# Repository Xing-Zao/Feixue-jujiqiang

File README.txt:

00_Priority README ------------- 技术文档，首先阅读
01_Firmware --------------------- 软件相关文件夹
02_Electronics -------------------- 电路相关文件夹
03_Machines --------------------- 机械相关文件夹
04_others ------------------------ 其他文件

README,txt --------------------- 每个分类文件夹都有，含有所处文件夹的阅读索引及必要说明，请最先阅读

相关源文件，软件可能不支持中文路径名，所以请先将项目名称改为中文

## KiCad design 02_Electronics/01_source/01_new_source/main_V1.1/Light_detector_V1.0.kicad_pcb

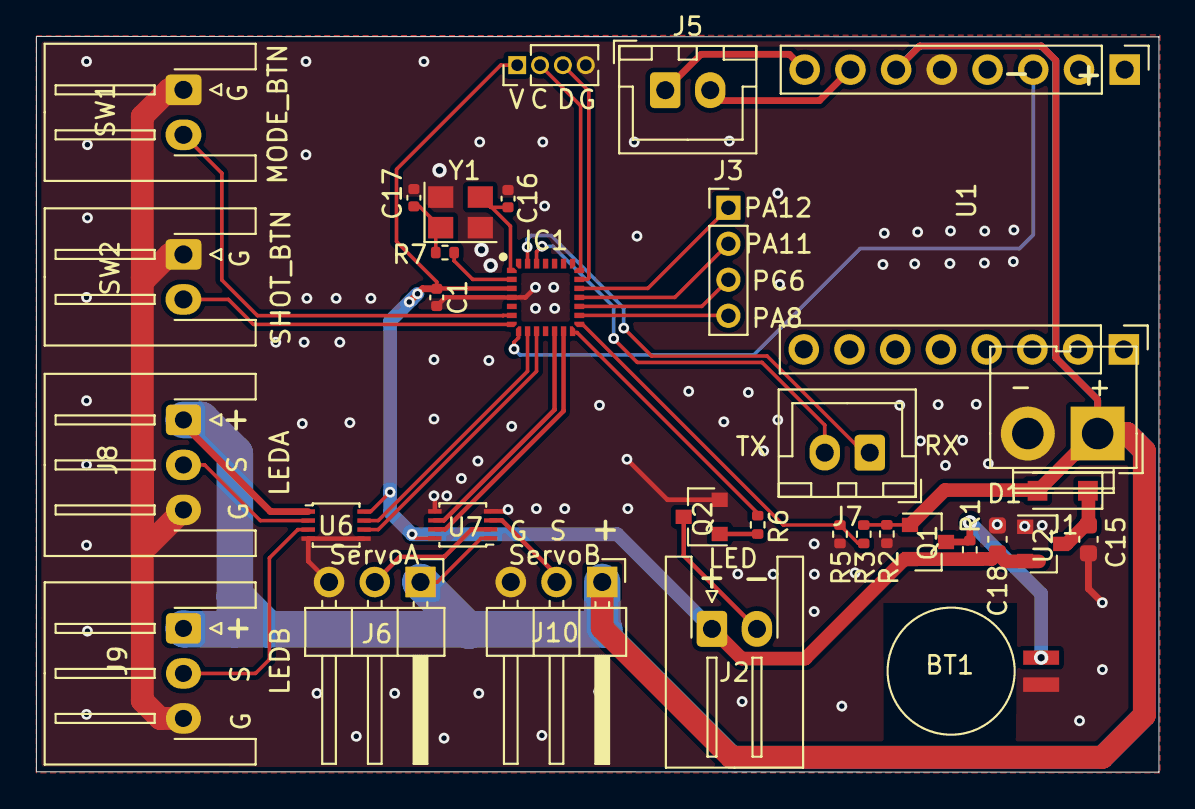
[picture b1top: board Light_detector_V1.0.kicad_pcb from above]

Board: 2 copper layers, 62.4 x 40.9 mm, 33 parts (0 on the bottom side), 33 nets.

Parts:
BT1: MS621FE; BatteryHolder_Seiko_MS621F
C1: 0.1uF; C_0402_1005Metric
C15, C18: 1uF; C_0603_1608Metric
C16, C17: 20pF; C_0402_1005Metric
D1: SS314F; D_SOD-123F
IC1: STM32G031G6U6; UFQFPN28
J1: POWER; JWT_A3963_1x02_P3.96mm_Vertical
J2: R_LED; JST_XH_S2B-XH-A-1_1x02_P2.50mm_Horizontal
J3: EXT; PinHeader_1x04_P2.00mm_Vertical
J4: SWD; PinHeader_1x04_P1.27mm_Vertical
J5: SPK; JST_XH_B2B-XH-A_1x02_P2.50mm_Vertical
J6: SERVOA; PinHeader_1x03_P2.54mm_Horizontal
J7: UART; JST_XH_B2B-XH-A_1x02_P2.50mm_Vertical
J8, J9: LEDA; JST_XH_S3B-XH-A-1_1x03_P2.50mm_Horizontal
J10: SERVOB; PinHeader_1x03_P2.54mm_Horizontal
Q1: AO3400; SOT-23
Q2: SS8050; SOT-23
R1: 680R; R_0402_1005Metric
R2: 100K; R_0402_1005Metric
R3, R5: 1M; R_0402_1005Metric
R6: 1K; R_0402_1005Metric
R7: 390R; R_0402_1005Metric
SW1: MODE_BTN; JST_XH_S2B-XH-A-1_1x02_P2.50mm_Horizontal
SW2: SHOT_BTN; JST_XH_S2B-XH-A-1_1x02_P2.50mm_Horizontal
U1: JQ8900-16P
U2: XC6206; SOT-23
U6, U7: SN74LVC2T45DCUR; VSSOP-8_2.4x2.1mm_P0.5mm
Y1: 8MHz; Crystal_SMD_3225-4Pin_3.2x2.5mm

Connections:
+3V3: C1.1, C18.1, IC1.3, J2.1, J4.1, Q1.2, R1.2, U2.2, U6.8, U7.8
+5V: D1.2, J1.1, J6.1, J8.1, J9.1, J10.1, Q1.1, R2.2, R3.2, U1.6, U6.1, U7.1
/5V_check: IC1.15, R3.1, R5.2
/LEDC_DI_IN: IC1.9, U6.7
/LEDC_DI_OUT: J8.2, U6.2
/LEDD_DI_IN: IC1.10, U6.6
/LEDD_DI_OUT: J9.2, U6.3
/LED_R: IC1.14, R6.1
/MODE_KEY: IC1.6, SW1.2
/OSC_IN: C16.2, IC1.1, Y1.3
/OSC_OUT: IC1.2, R7.2
/RX: IC1.27, J7.1
/SERVOA_IN: IC1.13, U7.7
/SERVOA_OUT: J6.2, U7.2
/SERVOB_IN: IC1.12, U7.6
/SERVOB_OUT: J10.2, U7.3
/SHOT_KEY: IC1.7, SW2.2
/SPK_TX: IC1.8, U1.3
/SWCLK: IC1.21, J4.2
/SWDIO: IC1.20, J4.3
/TX: IC1.26, J7.2
Earth: BT1.2, C1.2, C15.2, C16.1, C17.1, C18.2, IC1.4, J1.2, J4.4, J6.3, J8.3, J9.3, J10.3, Q2.2, R2.1, R5.1, SW1.1, SW2.1, U1.5, U2.1, U6.4, U6.5, U7.4, U7.5, Y1.2, Y1.4
unnamed: BT1.1, Q1.3, R1.1
unnamed: C15.1, D1.1, U2.3
unnamed: C17.2, R7.1, Y1.1
unnamed: IC1.16, J3.4
unnamed: IC1.17, J3.3
unnamed: IC1.18, J3.2
unnamed: IC1.19, J3.1
unnamed: J2.2, Q2.3
unnamed: J5.1, U1.8
unnamed: J5.2, U1.7
unnamed: Q2.1, R6.2

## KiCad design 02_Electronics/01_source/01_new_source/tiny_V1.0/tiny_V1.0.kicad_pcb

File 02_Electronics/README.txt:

01_source ----------------------------------------- 存放软件源码和已迭代源码

02_tools ------------------------------------------- 程序编写相关软件及使用文档

03_documents ------------------------------------ PCB设计参考文档，含元器件手册

04_others ----------------------------------------- 其他文件

README.txt  -------------------------------------- 每个文件夹下都有该文件，为所处文件夹的阅读索引及必要说明

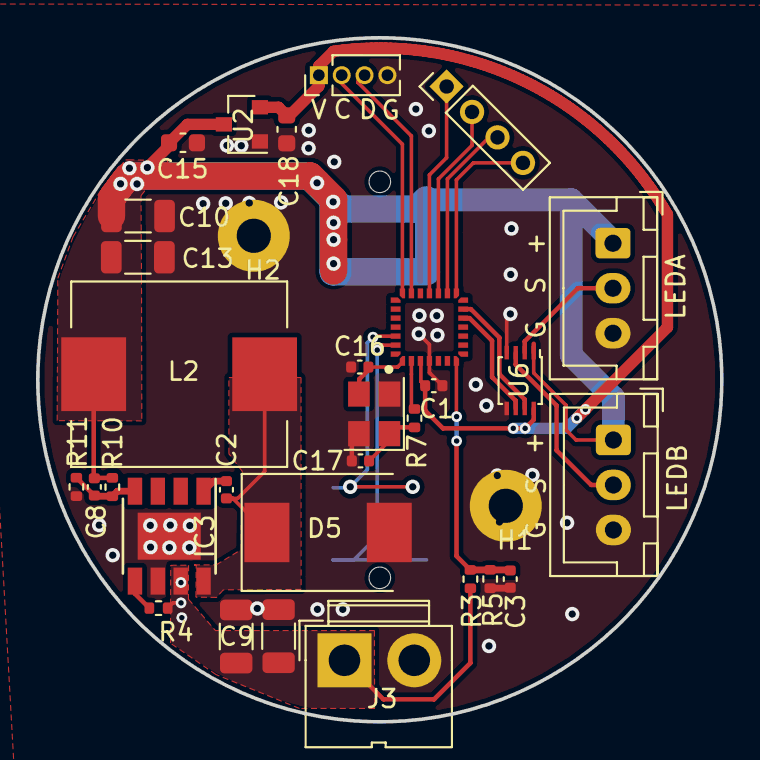
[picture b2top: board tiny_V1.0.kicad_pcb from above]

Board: 2 copper layers, 38.0 x 38.0 mm, 33 parts (1 on the bottom side), 24 nets.

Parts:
C1, C3: 0.1uF; C_0402_1005Metric
C2: 10nF; C_0402_1005Metric
C8: 82pF; C_0402_1005Metric
C9, C24: 4.7uF; C_1206_3216Metric
C10, C13: 22uF; C_1206_3216Metric
C15, C18: 1uF; C_0603_1608Metric
C16, C17: 20pF; C_0402_1005Metric
D5: B550C; D_SMC
H1, H2: MountingHole; MountingHole_1.5x4mm
IC1: STM32G031G6U6; UFQFPN28
IC3: RT8279GSP; Diodes_SO-8EP
J1: Conn_01x06; JL-6P-4.0PH-1.9H
J2: EXT; PinHeader_1x04_P2.00mm_Vertical
J3: Conn_01x02; JWT_A3963_1x02_P3.96mm_Vertical
J4: SWD; PinHeader_1x04_P1.27mm_Vertical
J8, J9: LEDA; JST_XH_B3B-XH-A_1x03_P2.50mm_Vertical
L2: 15uH; L_Neosid_SM-PIC1004H
R3: 2M; R_0402_1005Metric
R4, R10: 100K; R_0402_1005Metric
R5: 1M; R_0402_1005Metric
R7: 390R; R_0402_1005Metric
R11: 31.6k; R_0402_1005Metric
U2: XC6206; SOT-23
U6: SN74LVC2T45DCUR; VSSOP-8_2.4x2.1mm_P0.5mm
Y1: 8MHz; Crystal_SMD_3225-4Pin_3.2x2.5mm

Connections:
+3V3: C1.1, C18.1, IC1.3, J4.1, U2.2, U6.8
+5V: C8.2, C10.2, C13.2, C15.1, J1.1, J1.2, J8.1, J9.1, L2.2, R10.2, U2.3, U6.1
/BAT+: C9.1, C24.1, IC3.7, J3.1, R3.2, R4.1
/BAT_ADC: C3.1, IC1.7, R3.1, R5.2
/FB: C8.1, IC3.4, R10.1, R11.2
/LEDC_DI_IN: IC1.13, U6.7
/LEDC_DI_OUT: J8.2, U6.2
/LEDD_DI_IN: IC1.12, U6.6
/LEDD_DI_OUT: J9.2, U6.3
/OSC_IN: C16.2, IC1.1, Y1.3
/OSC_OUT: IC1.2, R7.2
/RX: IC1.27, J1.6
/SWCLK: IC1.21, J4.2
/SWDIO: IC1.20, J4.3
/TX: IC1.26, J1.5
Earth: C1.2, C3.2, C9.2, C10.1, C13.1, C15.2, C16.1, C17.1, C18.2, C24.2, D5.2, IC1.4, IC3.6, IC3.9, J1.3, J1.4, J3.2, J4.4, J8.3, J9.3, R5.1, R11.1, U2.1, U6.4, U6.5, Y1.2, Y1.4
unnamed: C2.1, D5.1, IC3.8, L2.1
unnamed: C2.2, IC3.1
unnamed: C17.2, R7.1, Y1.1
unnamed: IC1.15, J2.4
unnamed: IC1.16, J2.3
unnamed: IC1.17, J2.2
unnamed: IC1.18, J2.1
unnamed: IC3.5, R4.2

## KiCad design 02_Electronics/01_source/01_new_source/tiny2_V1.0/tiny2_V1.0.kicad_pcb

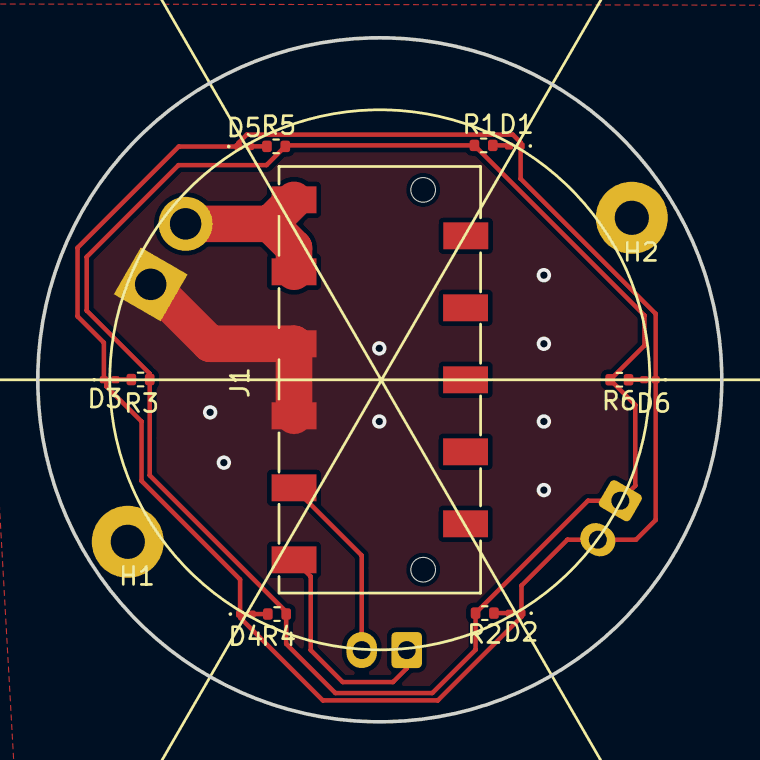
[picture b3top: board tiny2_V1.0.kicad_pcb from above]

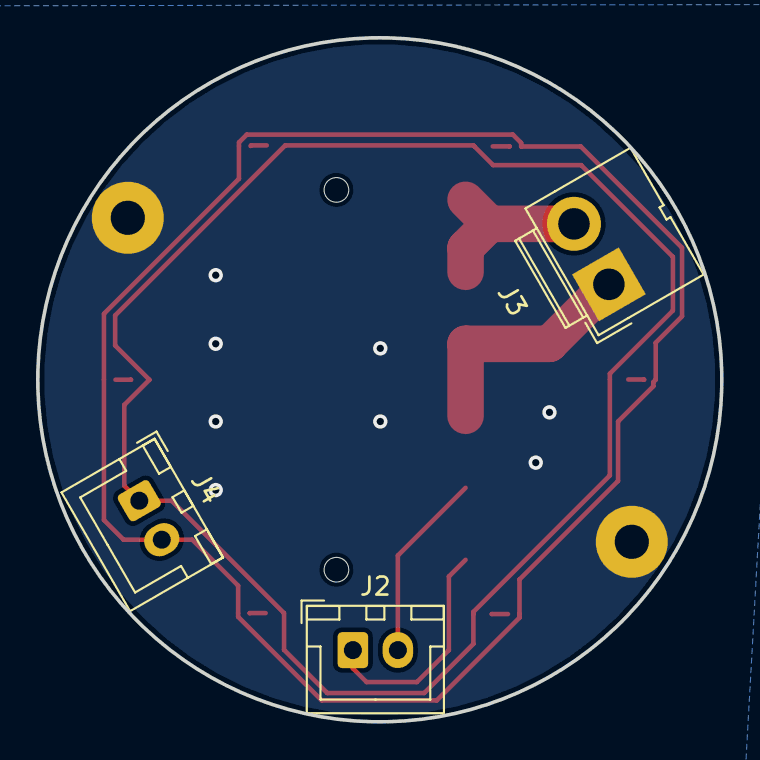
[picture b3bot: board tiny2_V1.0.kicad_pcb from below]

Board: 2 copper layers, 38.0 x 38.0 mm, 18 parts (3 on the bottom side), 12 nets.

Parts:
D1, D2, D3, D4, D5, D6: LED_Small; LED_0201_0603Metric
H1, H2: MountingHole; MountingHole_1.5x4mm
J1: Conn_01x06; JL-6P-4.0PH-5.65H
J2: UART; JST_XH_B2B-XH-A_1x02_P2.50mm_Vertical
J3: POWER; JWT_A3963_1x02_P3.96mm_Vertical
J4: LED; JST_XH_B2B-XH-A_1x02_P2.50mm_Vertical
R1, R2, R3, R4, R5, R6: R_Small; R_0402_1005Metric

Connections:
+5V: J1.1, J1.2, J3.2
Earth: J1.3, J1.4, J3.1
unnamed: D1.1, D2.1, D3.1, D4.1, D5.1, D6.1, J4.2
unnamed: D1.2, R1.1
unnamed: D2.2, R2.1
unnamed: D3.2, R3.1
unnamed: D4.2, R4.1
unnamed: D5.2, R5.1
unnamed: D6.2, R6.1
unnamed: J1.5, J2.2
unnamed: J1.6, J2.1
unnamed: J4.1, R1.2, R2.2, R3.2, R4.2, R5.2, R6.2
